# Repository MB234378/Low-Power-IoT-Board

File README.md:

Board Specifications:
 - 4 layers (Signal, GND, 3v3, Signal)
 - STM32L051 MCu
 - CC2500 rf transceiver
 - PCB antenna (see TI documentation SWRA118, DN035 for more info on PCB antennas)

Please note that this board is untested as of yet.

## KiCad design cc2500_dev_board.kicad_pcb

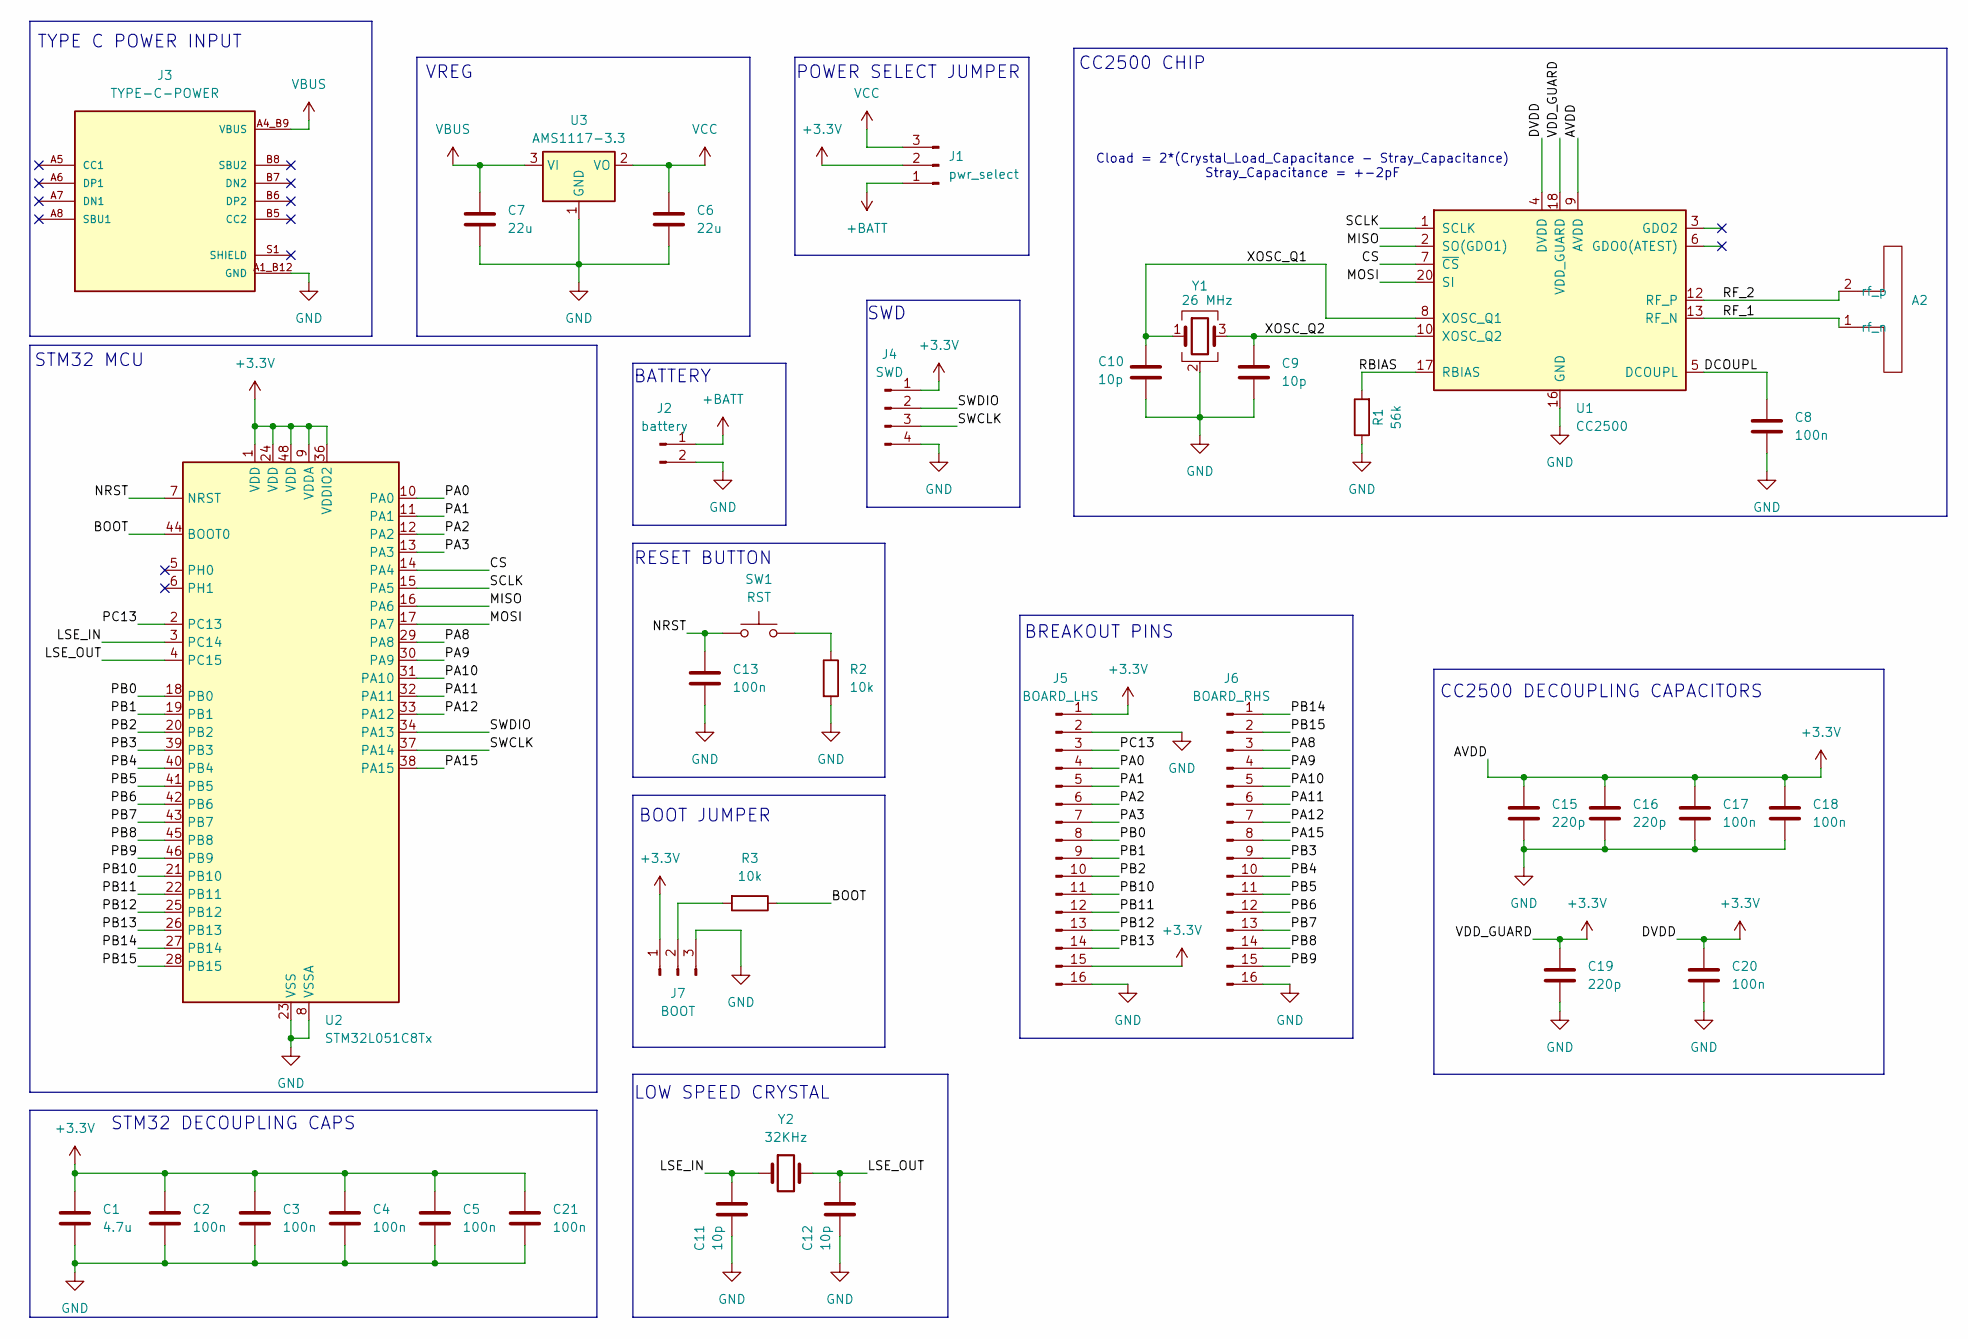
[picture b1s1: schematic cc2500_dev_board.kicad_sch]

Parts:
A2: FOLDED_DIPOLE_2.4
C1: 4.7u; C_0603_1608Metric
C2, C3, C4, C5, C8, C13, C17, C18, C20, C21: 100n; C_0402_1005Metric
C6, C7: 22u; C_0805_2012Metric
C9, C10, C11, C12: 10p; C_0402_1005Metric
C15, C16, C19: 220p; C_0402_1005Metric
J1: pwr_select; PinHeader_1x03_P2.54mm_Vertical
J2: battery; PinHeader_1x02_P2.54mm_Vertical
J3: TYPE-C-POWER; TYPE_C; PARTREV 2020.12.08
J4: SWD; PinHeader_1x04_P2.54mm_Vertical
J5: BOARD_LHS; PinHeader_1x16_P2.54mm_Vertical
J6: BOARD_RHS; PinHeader_1x16_P2.54mm_Vertical
J7: BOOT; PinHeader_1x03_P2.54mm_Vertical
R1: 56k; R_0402_1005Metric
R2, R3: 10k; R_0402_1005Metric
SW1: RST; Button_SMD
U1: CC2500; Texas_RGP0020H_VQFN-20-1EP_4x4mm_P0.5mm_EP2.4x2.4mm
U2: STM32L051C8Tx; LQFP-48_7x7mm_P0.5mm
U3: AMS1117-3.3; SOT-223-3_TabPin2
Y1: 26 MHz; Crystal_SMD_3225-4Pin_3.2x2.5mm
Y2: 32KHz; XTAL_FC-135_EPS

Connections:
+3.3V: C1.1, C2.1, C3.1, C4.1, C5.1, C15.1, C16.1, C17.1, C18.1, C19.1, C20.1, C21.1, J1.2, J4.1, J5.1, J5.15, J7.1, U1.4 (DVDD), U1.9 (AVDD), U1.11 (AVDD), U1.14 (AVDD), U1.15 (AVDD), U1.18 (VDD_GUARD), U2.1 (VDD), U2.9 (VDDA), U2.24 (VDD), U2.36 (VDDIO2), U2.48 (VDD)
+BATT: J1.1, J2.1
/BOOT: R3.1, U2.44 (BOOT0)
/CS: U1.7 (~CS), U2.14 (PA4)
/DCOUPL: C8.1, U1.5 (DCOUPL)
/LSE_IN: C11.2, U2.3 (PC14), Y2.1
/LSE_OUT: C12.2, U2.4 (PC15), Y2.2
/MISO: U1.2 (SO(GDO1)), U2.16 (PA6)
/MOSI: U1.20 (SI), U2.17 (PA7)
/NRST: C13.1, SW1.1, U2.7 (NRST)
/PA0: J5.4, U2.10 (PA0)
/PA1: J5.5, U2.11 (PA1)
/PA2: J5.6, U2.12 (PA2)
/PA3: J5.7, U2.13 (PA3)
/PA8: J6.3, U2.29 (PA8)
/PA9: J6.4, U2.30 (PA9)
/PA10: J6.5, U2.31 (PA10)
/PA11: J6.6, U2.32 (PA11)
/PA12: J6.7, U2.33 (PA12)
/PA15: J6.8, U2.38 (PA15)
/PB0: J5.8, U2.18 (PB0)
/PB1: J5.9, U2.19 (PB1)
/PB2: J5.10, U2.20 (PB2)
/PB3: J6.9, U2.39 (PB3)
/PB4: J6.10, U2.40 (PB4)
/PB5: J6.11, U2.41 (PB5)
/PB6: J6.12, U2.42 (PB6)
/PB7: J6.13, U2.43 (PB7)
/PB8: J6.14, U2.45 (PB8)
/PB9: J6.15, U2.46 (PB9)
/PB10: J5.11, U2.21 (PB10)
/PB11: J5.12, U2.22 (PB11)
/PB12: J5.13, U2.25 (PB12)
/PB13: J5.14, U2.26 (PB13)
/PB14: J6.1, U2.27 (PB14)
/PB15: J6.2, U2.28 (PB15)
/PC13: J5.3, U2.2 (PC13)
/RBIAS: R1.2, U1.17 (RBIAS)
/RF_1: A2.1 (rf_n), U1.13 (RF_N)
/RF_2: A2.2 (rf_p), U1.12 (RF_P)
/SCLK: U1.1 (SCLK), U2.15 (PA5)
/SWCLK: J4.3, U2.37 (PA14)
/SWDIO: J4.2, U2.34 (PA13)
/XOSC_Q1: C10.1, U1.8 (XOSC_Q1), Y1.1
/XOSC_Q2: C9.1, U1.10 (XOSC_Q2), Y1.3
GND: C1.2, C2.2, C3.2, C4.2, C5.2, C6.2, C7.2, C8.2, C9.2, C10.2, C11.1, C12.1, C13.2, C15.2, C16.2, C17.2, C18.2, C19.2, C20.2, C21.2, J2.2, J3.A1_B12 (GND), J3.B1_A12 (GND), J4.4, J5.2, J5.16, J6.16, J7.3, R1.1, R2.2, U1.16 (GND), U1.19 (GND), U1.21 (GND), U2.8 (VSSA), U2.23 (VSS), U2.35 (VSS), U2.47 (VSS), U3.1 (GND), Y1.2 (G), Y1.4 (G)
unnamed: J7.2, R3.2
unnamed: R2.1, SW1.2
VBUS: C7.1, J3.A4_B9 (VBUS), J3.B4_A9 (VBUS), U3.3 (VI)
VCC: C6.1, J1.3, U3.2 (VO)

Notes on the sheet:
RESET BUTTON
VREG
TYPE C POWER INPUT
BREAKOUT PINS
STM32 MCU
SWD
LOW SPEED CRYSTAL
STM32 DECOUPLING CAPS
BOOT JUMPER
POWER SELECT JUMPER
BATTERY
Cload = 2*(Crystal_Load_Capacitance - Stray_Capacitance) Stray_Capacitance = +-2pF
CC2500 CHIP
CC2500 DECOUPLING CAPACITORS

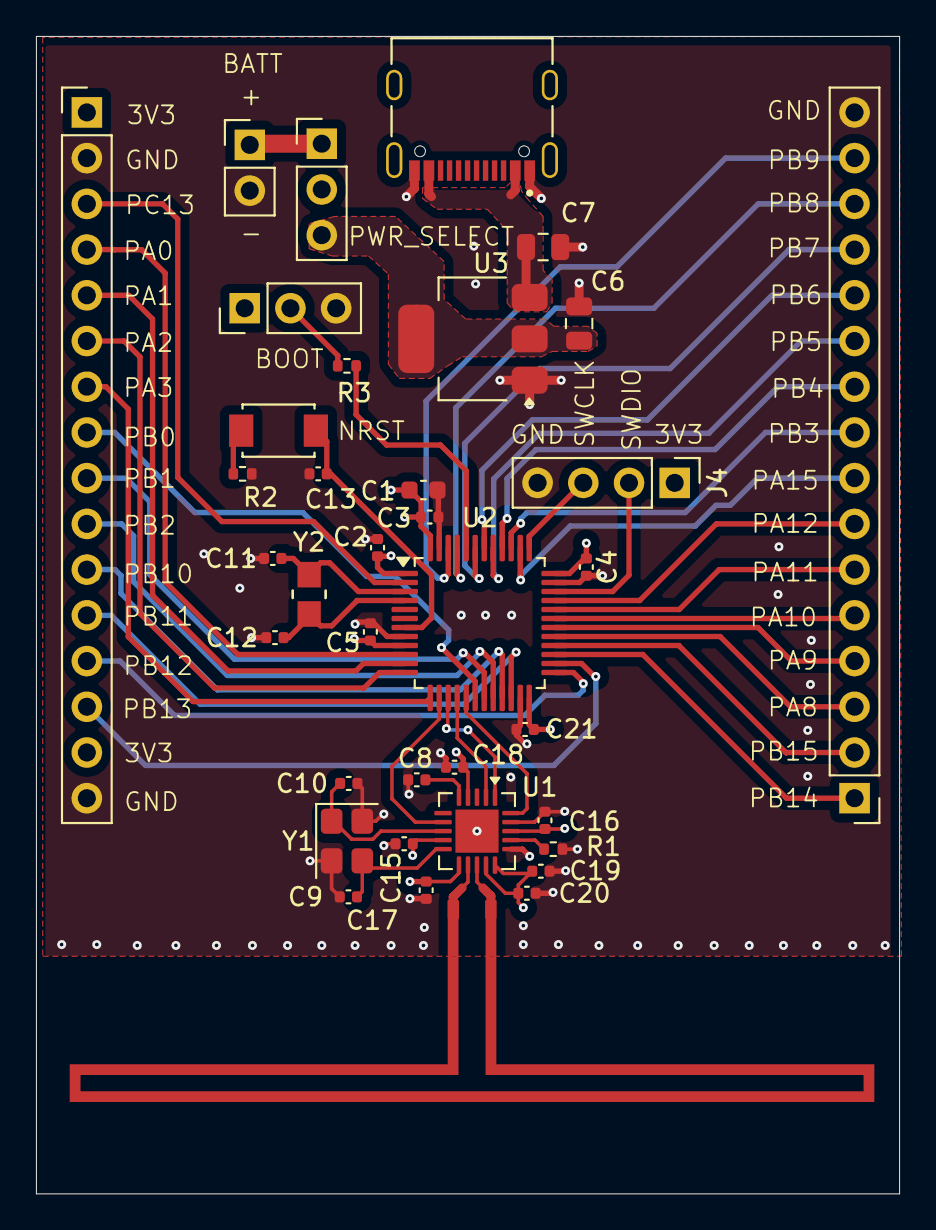
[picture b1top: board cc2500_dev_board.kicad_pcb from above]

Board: 4 copper layers, 47.9 x 64.3 mm, 37 parts (0 on the bottom side), 50 nets.

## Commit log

2026-03-08 Add board specifications and image to README
    Added board specifications and image to README.
